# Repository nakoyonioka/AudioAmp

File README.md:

# Stereo Audio Amplifier (TPA3144D2)

This project implements a stereo audio amplifier circuit suitable for driving passive speakers. It utilizes the efficient Class-D architecture of the TPA3144D2, known for its low power consumption and relatively simple implementation.

## Features

* **Amplifier IC:** Based on the Texas Instruments TPA3144D2 stereo Class-D audio amplifier.
* **Output Power:** Capable of delivering up to 6W(details depend on power supply voltage and load impedance - refer to TPA3144D2 datasheet).
* **Stereo Output:** Provides two independent channels for stereo audio amplification.
* **Input Interface:** Designed for line-level stereo audio input.
* **Volume Control:** Includes interface points for connecting external potentiometers for independent left and right channel volume control.
* **Power Input:** Standard connector for DC power supply.
* **Speaker Outputs:** Screw terminals for easy connection of passive speakers.
* **Shutdown/Standby Control:** Includes provision for controlling the amplifier's operational state.

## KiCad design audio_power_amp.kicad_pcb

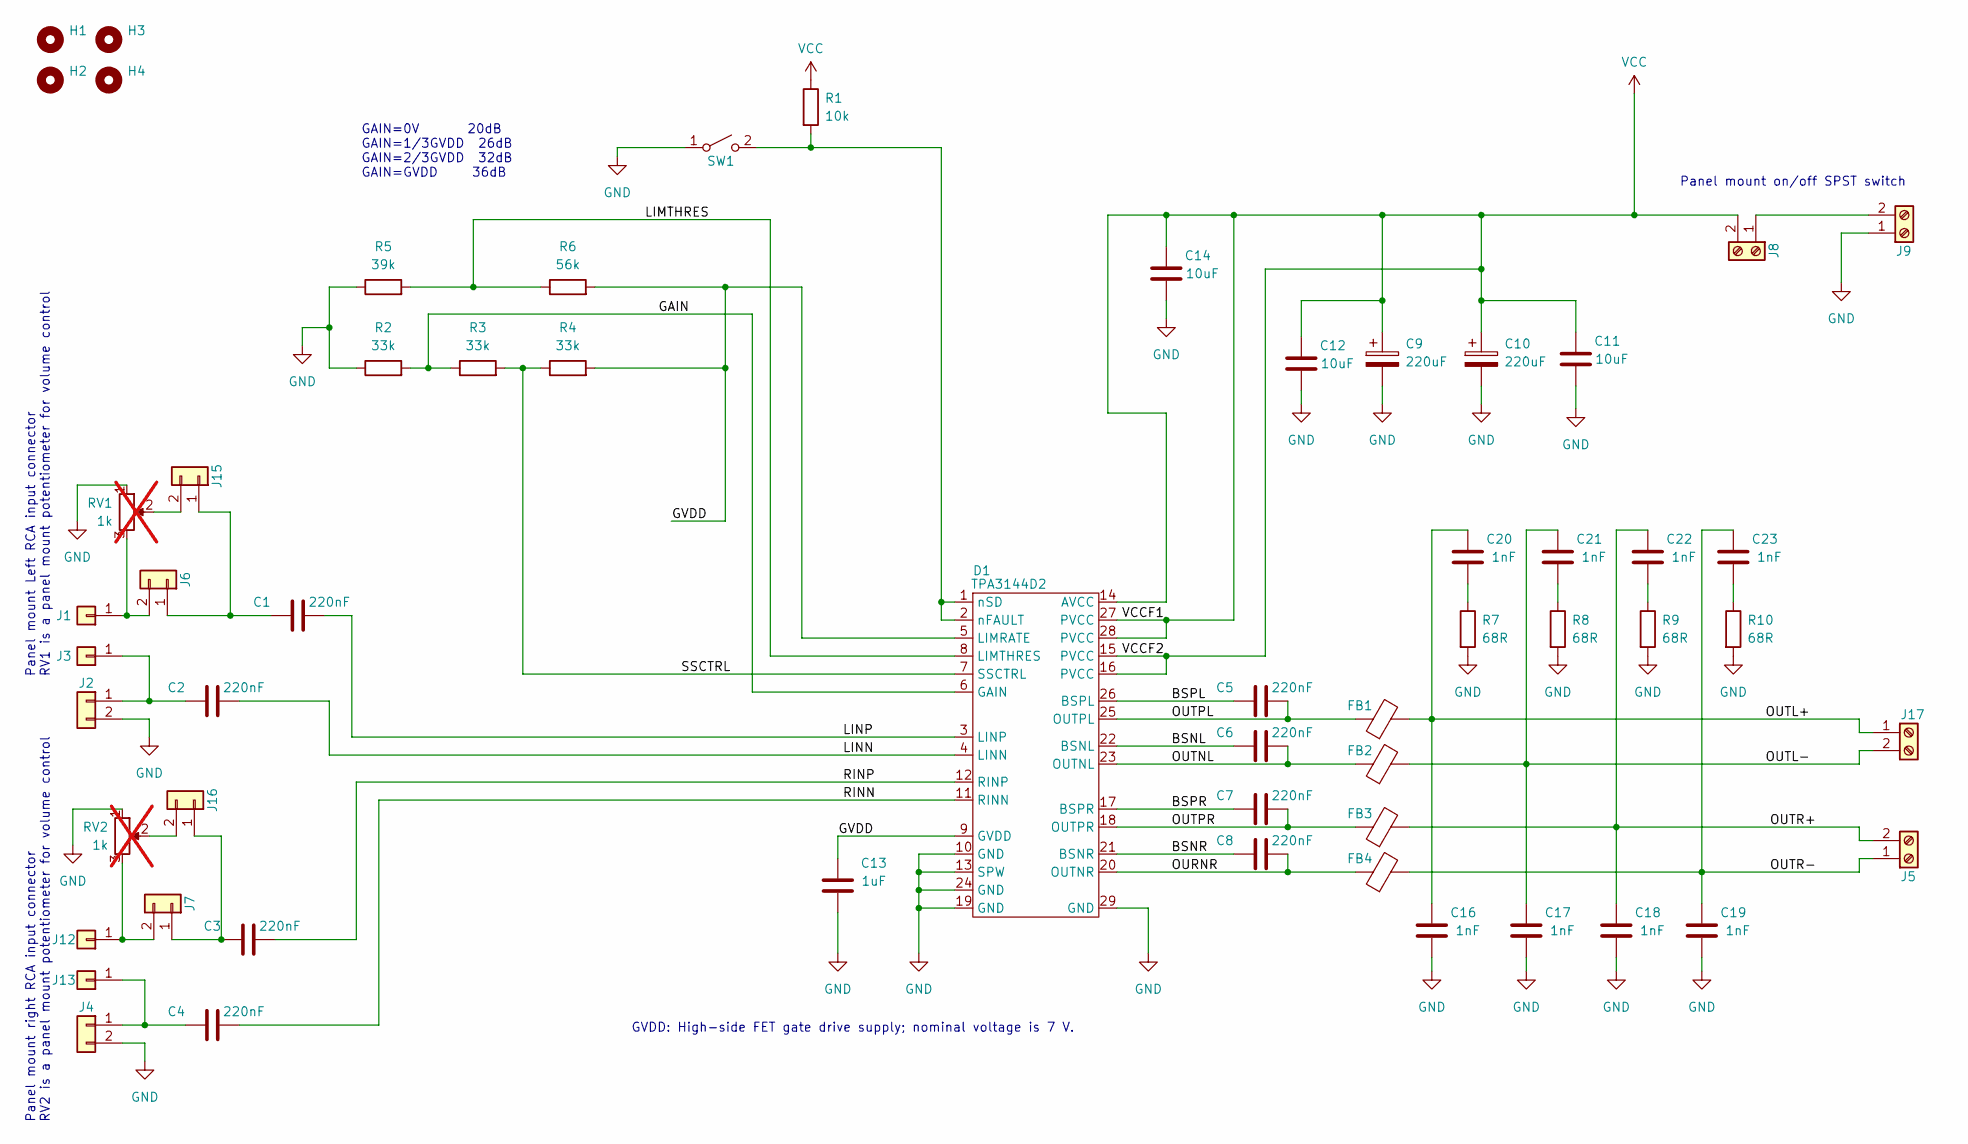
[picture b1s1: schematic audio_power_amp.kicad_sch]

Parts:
C1, C2, C3, C4: 220nF; C_0603_1608Metric_Pad1.08x0.95mm_HandSolder; LCSC PN C21120
C5, C6, C7, C8: 220nF; C_0603_1608Metric_Pad1.08x0.95mm_HandSolder; JLCPCB Type Basic
C9, C10: 220uF; CP_Radial_D10.0mm_P3.50mm
C11, C12, C14: 10uF; C_0805_2012Metric_Pad1.18x1.45mm_HandSolder; LCSC PN C440198
C13: 1uF; C_0603_1608Metric_Pad1.08x0.95mm_HandSolder; LCSC PN C15849
C16, C17, C18, C19, C20, C21, C22, C23: 1nF; C_0603_1608Metric_Pad1.08x0.95mm_HandSolder; LCSC PN C1588
D1: TPA3144D2; HTSSOP-28-1EP_4.4x9.7mm_P0.65mm_EP3.4x9.5mm_ThermalVias; LCSC PN C2860192
FB1, FB2, FB3, FB4: NFZ2MSM301SN10L; L_0805_2012Metric_Pad1.15x1.40mm_HandSolder; LCSC PN C668489
H1, H2, H3, H4: MountingHole; MountingHole_3.2mm_M3
J1, J3, J12, J13: Conn_01x01; PinHeader_1x01_P2.54mm_Vertical
J2, J4, J6, J7, J15, J16: Conn_01x02; PinHeader_1x02_P2.54mm_Vertical
J5, J8, J9, J17: Screw_Terminal_01x02; TerminalBlock_MetzConnect_Type086_RT03402HBLC_1x02_P3.81mm_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
R1: 10k; R_0805_2012Metric_Pad1.20x1.40mm_HandSolder; LCSC PN C17414
R2, R3, R4: 33k; R_0603_1608Metric_Pad0.98x0.95mm_HandSolder; LCSC PN C4216
R5: 39k; R_0603_1608Metric_Pad0.98x0.95mm_HandSolder; LCSC PN C23153
R6: 56k; R_0603_1608Metric_Pad0.98x0.95mm_HandSolder; LCSC PN C23206
R7, R8, R9, R10: 68R; R_0805_2012Metric_Pad1.20x1.40mm_HandSolder; LCSC PN C17802
RV1, RV2: 1k; PinHeader_1x03_P2.54mm_Vertical; not fitted
SW1: SW_SPST; SW_Tactile_Straight_KSA0Axx1LFTR

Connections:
/BSNL: C6.1, D1.22 (BSNL)
/BSNR: C8.1, D1.21 (BSNR)
/BSPL: C5.1, D1.26 (BSPL)
/BSPR: C7.1, D1.17 (BSPR)
/GAIN: D1.6 (GAIN), R2.2, R3.1
/GVDD: C13.2, D1.5 (LIMRATE), D1.9 (GVDD), R4.2, R6.2
/LIMTHRES: D1.8 (LIMTHRES), R5.2, R6.1
/LINN: C2.2, D1.4 (LINN)
/LINP: C1.2, D1.3 (LINP)
/OURNR: C8.2, D1.20 (OUTNR), FB4.1
/OUTL+: C16.2, C20.2, FB1.2, J17.1
/OUTL-: C17.2, C21.2, FB2.2, J17.2
/OUTNL: C6.2, D1.23 (OUTNL), FB2.1
/OUTPL: C5.2, D1.25 (OUTPL), FB1.1
/OUTPR: C7.2, D1.18 (OUTPR), FB3.1
/OUTR+: C18.2, C22.2, FB3.2, J5.2
/OUTR-: C19.2, C23.2, FB4.2, J5.1
/RINN: C4.2, D1.11 (RINN)
/RINP: C3.2, D1.12 (RINP)
/SSCTRL: D1.7 (SSCTRL), R3.2, R4.1
GND: C9.2, C10.2, C11.1, C12.1, C13.1, C14.1, C16.1, C17.1, C18.1, C19.1, D1.10 (GND), D1.13 (SPW), D1.19 (GND), D1.24 (GND), D1.29 (GND), J2.2, J4.2, J9.1, R2.1, R5.1, R7.2, R8.2, R9.2, R10.2, RV1.1, RV2.1, SW1.1 (A)
unnamed: C20.1, R7.1
unnamed: C21.1, R8.1
unnamed: C22.1, R9.1
unnamed: C23.1, R10.1
unnamed: D1.1 (nSD), D1.2 (nFAULT), R1.2, SW1.2 (B)
unnamed: J1.1, J6.2, RV1.3
unnamed: C2.1, J2.1, J3.1
unnamed: J8.1, J9.2
unnamed: J7.2, J12.1, RV2.3
unnamed: C4.1, J4.1, J13.1
unnamed: C1.1, J6.1, J15.1
unnamed: J15.2, RV1.2
unnamed: C3.1, J7.1, J16.1
unnamed: J16.2, RV2.2
VCC: C9.1, C10.1, C11.2, C12.2, C14.2, D1.14 (AVCC), D1.15 (PVCC), D1.16 (PVCC), D1.27 (PVCC), D1.28 (PVCC), J8.2, R1.1

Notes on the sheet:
GVDD: High-side FET gate drive supply; nominal voltage is 7 V.
Panel mount Left RCA input connector RV1 is a panel mount potentiometer for volume control
GAIN=0V 20dB GAIN=1/3GVDD 26dB GAIN=2/3GVDD 32dB GAIN=GVDD 36dB
Panel mount right RCA input connector RV2 is a panel mount potentiometer for volume control
Panel mount on/off SPST switch

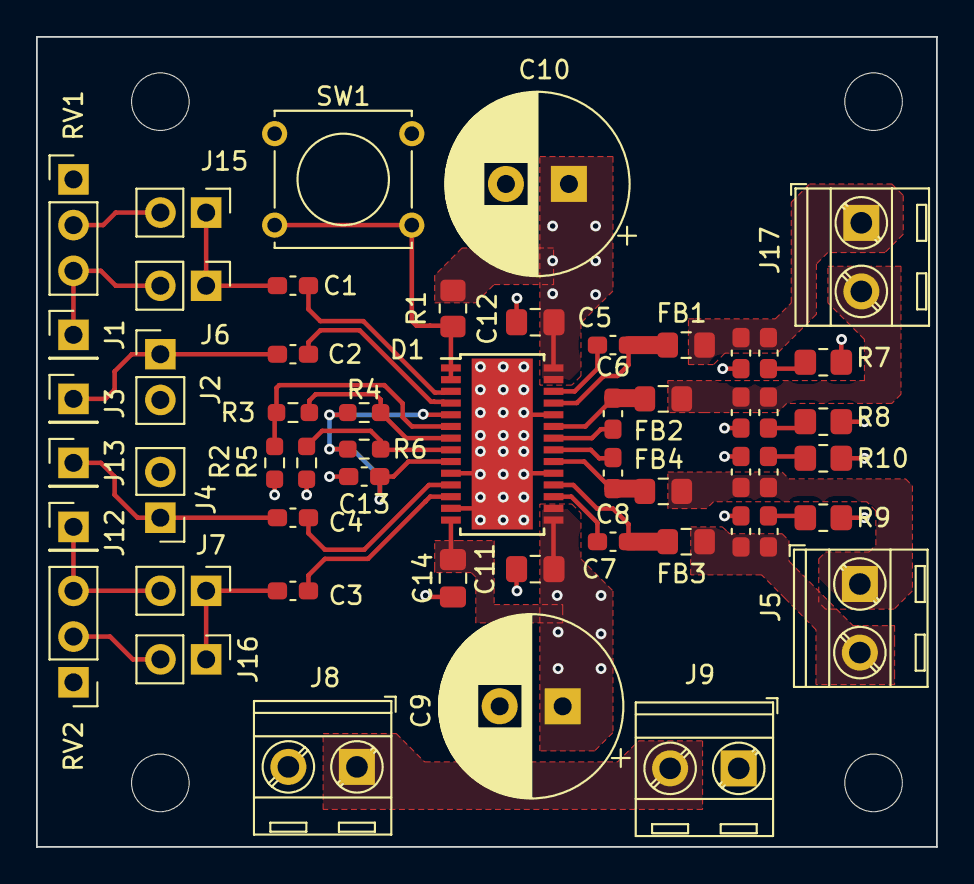
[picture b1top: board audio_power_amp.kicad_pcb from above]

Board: 4 copper layers, 50.0 x 45.0 mm, 58 parts (0 on the bottom side), 36 nets.

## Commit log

2025-05-06 push design files
